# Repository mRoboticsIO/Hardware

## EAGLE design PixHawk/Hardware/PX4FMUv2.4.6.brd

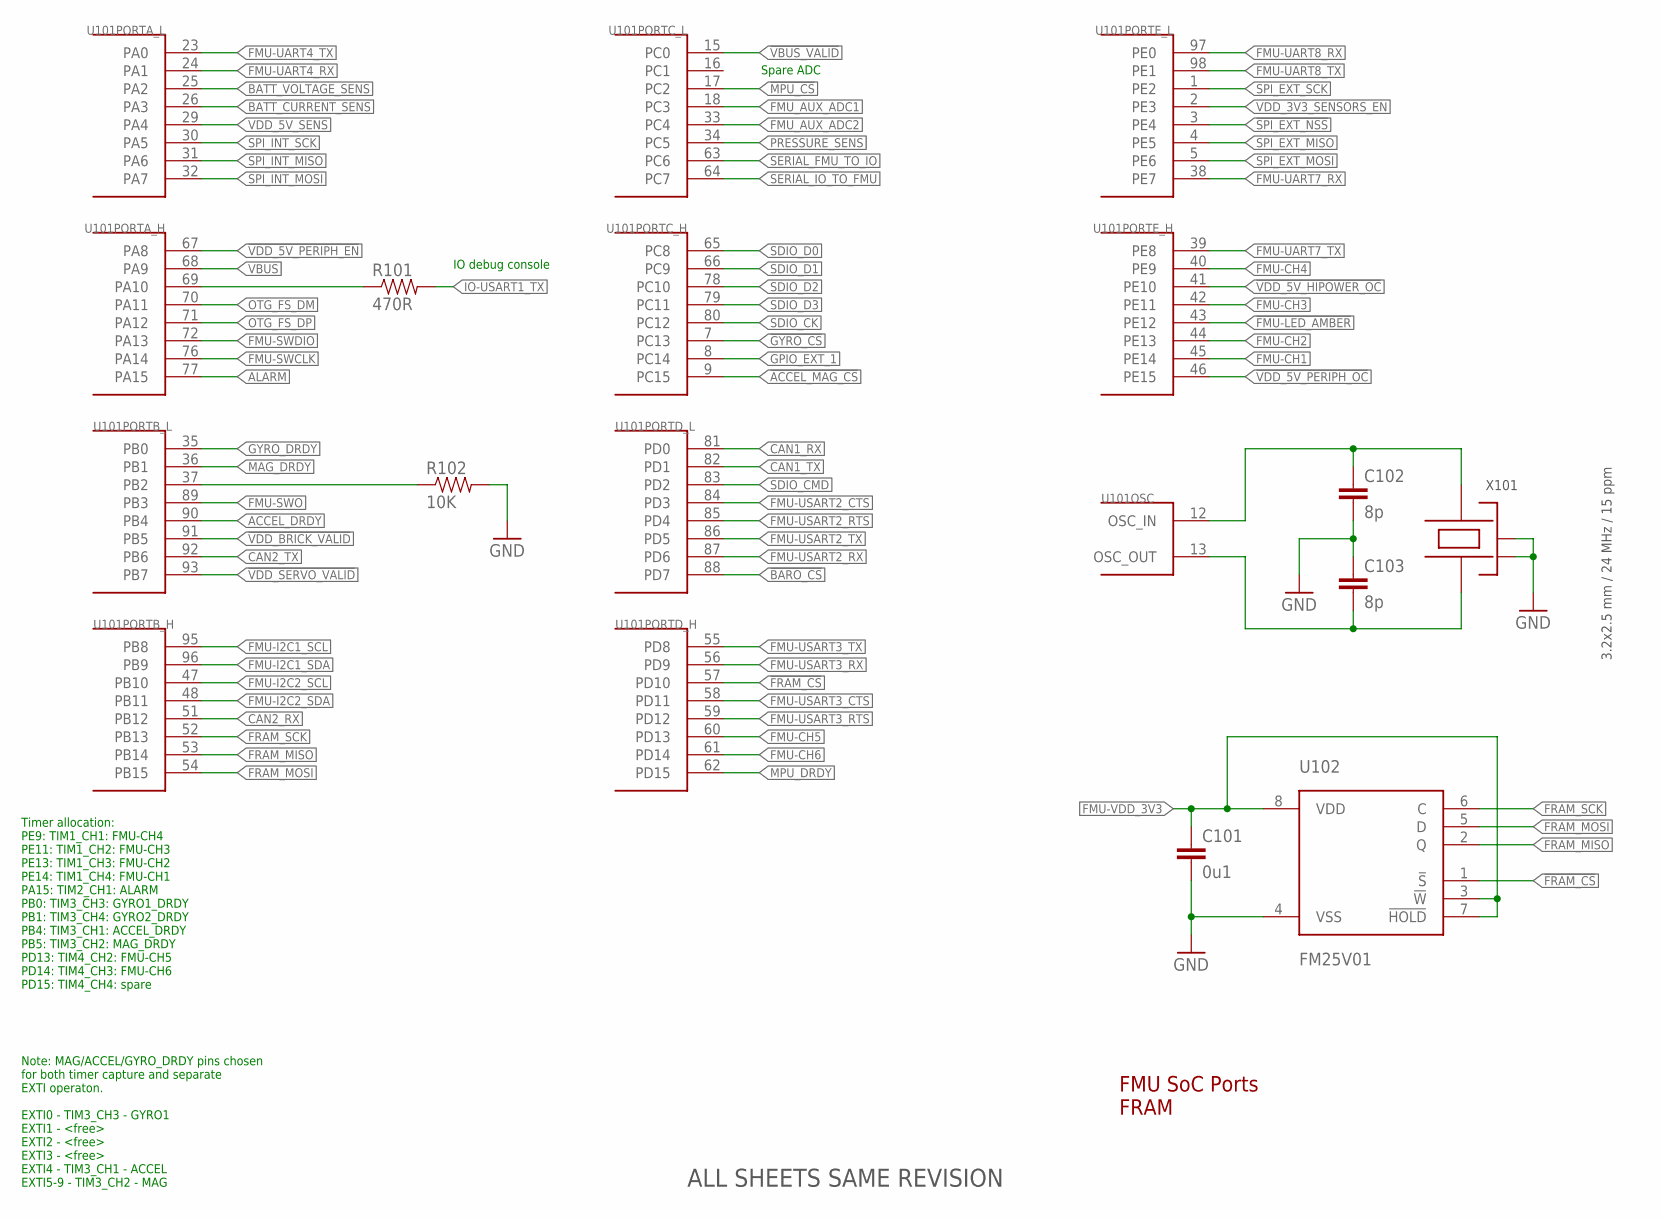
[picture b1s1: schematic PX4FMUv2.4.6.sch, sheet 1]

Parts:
C101: 0u1; 0402-CAP; PARTNO CC0402ZRY5V7BB104
C102, C103: 8p; 0402-CAP; PARTNO C1005C0G1H080C
R101: 470R; 0402-RES; PARTNO RC0402FR-07470RL
R102: 10K; 0402-RES; PARTNO RC0402FR-0710KL
U101: STM32F4X7VX; TQFP100; PARTNO STM32F427VI
U102: FM25V01; SO08; PARTNO FM25V01-G
X101: 3.2x2.5 mm / 24 MHz / 15 ppm; OSCILLATOR-3.2X2.5; PARTNO NX3225SA-24.000000MHZ

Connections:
!ACCEL_MAG_CS: U101.9 (PC15); also elsewhere on the board
!BARO_CS: U101.88 (PD7); also elsewhere on the board
!FMU-LED_AMBER: U101.43 (PE12); also elsewhere on the board
!FRAM_CS: U101.57 (PD10), U102.1 (!S)
!GYRO_CS: U101.7 (PC13); also elsewhere on the board
!MPU_CS: U101.17 (PC2); also elsewhere on the board
!SPI_EXT_NSS: U101.3 (PE4); also elsewhere on the board
!VBUS_VALID: U101.15 (PC0); also elsewhere on the board
!VDD_5V_HIPOWER_OC: U101.41 (PE10); also elsewhere on the board
!VDD_5V_PERIPH_EN: U101.67 (PA8); also elsewhere on the board
!VDD_5V_PERIPH_OC: U101.46 (PE15); also elsewhere on the board
!VDD_BRICK_VALID: U101.91 (PB5); also elsewhere on the board
!VDD_SERVO_VALID: U101.93 (PB7); also elsewhere on the board
ACCEL_DRDY: U101.90 (PB4); also elsewhere on the board
ALARM: U101.77 (PA15); also elsewhere on the board
BATT_CURRENT_SENS: U101.26 (PA3); also elsewhere on the board
BATT_VOLTAGE_SENS: U101.25 (PA2); also elsewhere on the board
CAN1_RX: U101.81 (PD0); also elsewhere on the board
CAN1_TX: U101.82 (PD1); also elsewhere on the board
CAN2_RX: U101.51 (PB12); also elsewhere on the board
CAN2_TX: U101.92 (PB6); also elsewhere on the board
FMU-CH1: U101.45 (PE14); also elsewhere on the board
FMU-CH2: U101.44 (PE13); also elsewhere on the board
FMU-CH3: U101.42 (PE11); also elsewhere on the board
FMU-CH4: U101.40 (PE9); also elsewhere on the board
FMU-CH5: U101.60 (PD13); also elsewhere on the board
FMU-CH6: U101.61 (PD14); also elsewhere on the board
FMU-I2C1_SCL: U101.95 (PB8); also elsewhere on the board
FMU-I2C1_SDA: U101.96 (PB9); also elsewhere on the board
FMU-I2C2_SCL: U101.47 (PB10); also elsewhere on the board
FMU-I2C2_SDA: U101.48 (PB11); also elsewhere on the board
FMU-SWCLK: U101.76 (PA14); also elsewhere on the board
FMU-SWDIO: U101.72 (PA13); also elsewhere on the board
FMU-SWO: U101.89 (PB3); also elsewhere on the board
FMU-UART4_RX: U101.24 (PA1); also elsewhere on the board
FMU-UART4_TX: U101.23 (PA0); also elsewhere on the board
FMU-UART7_RX: U101.38 (PE7); also elsewhere on the board
FMU-UART7_TX: U101.39 (PE8); also elsewhere on the board
FMU-UART8_RX: U101.97 (PE0); also elsewhere on the board
FMU-UART8_TX: U101.98 (PE1); also elsewhere on the board
FMU-USART2_CTS: U101.84 (PD3); also elsewhere on the board
FMU-USART2_RTS: U101.85 (PD4); also elsewhere on the board
FMU-USART2_RX: U101.87 (PD6); also elsewhere on the board
FMU-USART2_TX: U101.86 (PD5); also elsewhere on the board
FMU-USART3_CTS: U101.58 (PD11); also elsewhere on the board
FMU-USART3_RTS: U101.59 (PD12); also elsewhere on the board
FMU-USART3_RX: U101.56 (PD9); also elsewhere on the board
FMU-USART3_TX: U101.55 (PD8); also elsewhere on the board
FMU-VDD_3V3: C101.P$1 (1), U102.3 (!W), U102.7 (!HOLD), U102.8 (VDD); also elsewhere on the board
FMU_AUX_ADC1: U101.18 (PC3); also elsewhere on the board
FMU_AUX_ADC2: U101.33 (PC4); also elsewhere on the board
FRAM_MISO: U101.53 (PB14), U102.2 (Q)
FRAM_MOSI: U101.54 (PB15), U102.5 (D)
FRAM_SCK: U101.52 (PB13), U102.6 (C)
GND: C101.P$2 (2), C102.P$2 (2), C103.P$1 (1), R102.P$2 (2), U102.4 (VSS), X101.2 (NC_2), X101.4 (NC_4); also elsewhere on the board
GPIO_EXT_1: U101.8 (PC14); also elsewhere on the board
GYRO_DRDY: U101.35 (PB0); also elsewhere on the board
IO-USART1_TX: R101.P$2 (2); also elsewhere on the board
MAG_DRDY: U101.36 (PB1); also elsewhere on the board
MPU_DRDY: U101.62 (PD15); also elsewhere on the board
unnamed: C103.P$2 (2), U101.13 (OSC_OUT), X101.1
unnamed: C102.P$1 (1), U101.12 (OSC_IN), X101.3
unnamed: R101.P$1 (1), U101.69 (PA10)
OTG_FS_DM: U101.70 (PA11); also elsewhere on the board
OTG_FS_DP: U101.71 (PA12); also elsewhere on the board
PB2-BOOT1: R102.P$1 (1), U101.37 (PB2)
PRESSURE_SENS: U101.34 (PC5); also elsewhere on the board
SDIO_CK: U101.80 (PC12); also elsewhere on the board
SDIO_CMD: U101.83 (PD2); also elsewhere on the board
SDIO_D0: U101.65 (PC8); also elsewhere on the board
SDIO_D1: U101.66 (PC9); also elsewhere on the board
SDIO_D2: U101.78 (PC10); also elsewhere on the board
SDIO_D3: U101.79 (PC11); also elsewhere on the board
SERIAL_FMU_TO_IO: U101.63 (PC6); also elsewhere on the board
SERIAL_IO_TO_FMU: U101.64 (PC7); also elsewhere on the board
SPI_EXT_MISO: U101.4 (PE5); also elsewhere on the board
SPI_EXT_MOSI: U101.5 (PE6); also elsewhere on the board
SPI_EXT_SCK: U101.1 (PE2); also elsewhere on the board
SPI_INT_MISO: U101.31 (PA6); also elsewhere on the board
SPI_INT_MOSI: U101.32 (PA7); also elsewhere on the board
SPI_INT_SCK: U101.30 (PA5); also elsewhere on the board
VBUS: U101.68 (PA9); also elsewhere on the board
VDD_3V3_SENSORS_EN: U101.2 (PE3); also elsewhere on the board
VDD_5V_SENS: U101.29 (PA4); also elsewhere on the board

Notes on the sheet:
FMU SoC Ports FRAM
Note: MAG/ACCEL/GYRO_DRDY pins chosen for both timer capture and separate EXTI operaton. EXTI0 - TIM3_CH3 - GYRO1 EXTI1 - <free> EXTI2 - <free> EXTI3 - <free> EXTI4 - TIM3_CH1 - ACCEL EXTI5-9 - TIM3_CH2 - MAG
Timer allocation: PE9: TIM1_CH1: FMU-CH4 PE11: TIM1_CH2: FMU-CH3 PE13: TIM1_CH3: FMU-CH2 PE14: TIM1_CH4: FMU-CH1 PA15: TIM2_CH1: ALARM PB0: TIM3_CH3: GYRO1_DRDY PB1: TIM3_CH4: GYRO2_DRDY PB4: TIM3_CH1: ACCEL_DRDY PB5: TIM3_CH2: MAG_DRDY PD13: TIM4_CH2: FMU-CH5 PD14: TIM4_CH3: FMU-CH6 PD15: TIM4_CH4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
IO debug console
Spare ADC
ALL SHEETS SAME REVISION

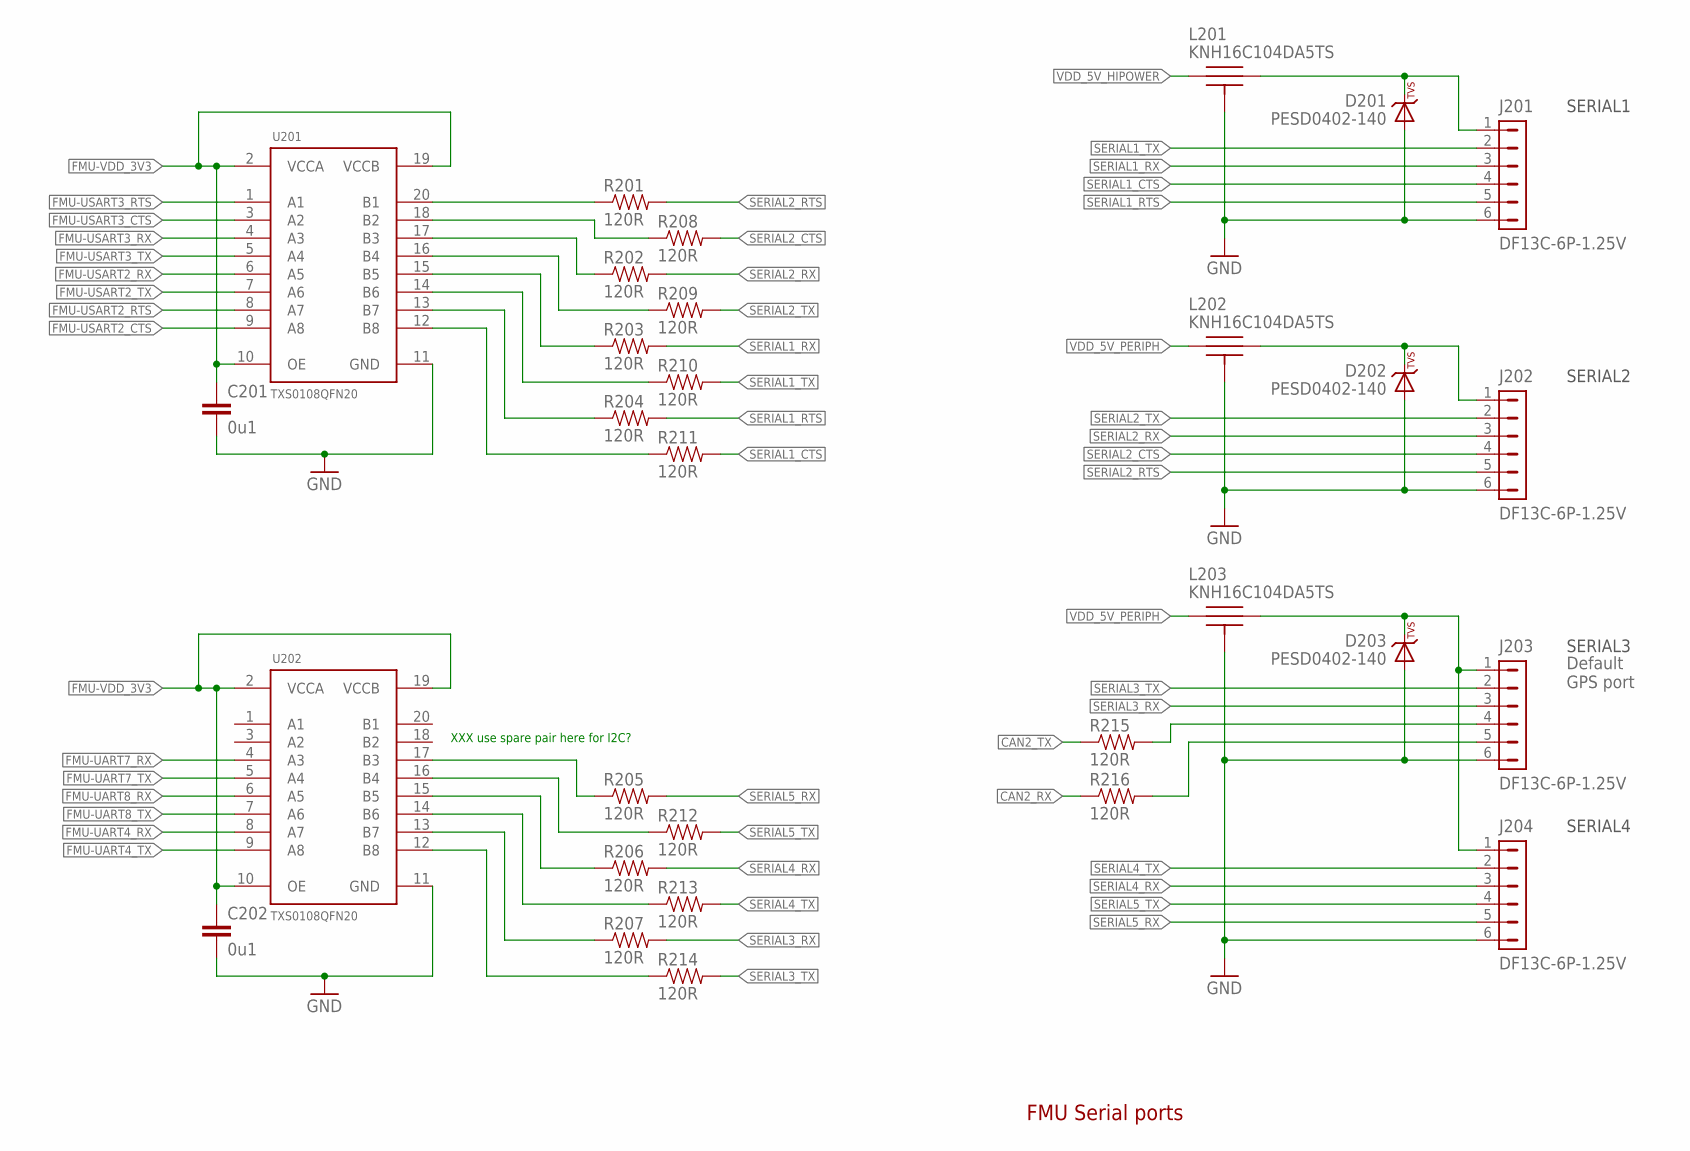
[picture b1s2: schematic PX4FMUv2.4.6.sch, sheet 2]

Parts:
C201, C202: 0u1; 0402-CAP; PARTNO CC0402ZRY5V7BB104
D201, D202, D203: PESD0402-140; 0402-TVS; PARTNO PESD0402-140
J201, J202, J203, J204: DF13C-6P-1.25V; PARTNO DF13C-6P-1.25V(20)
L201, L202, L203: KNH16C104DA5TS; KYOCERA-KNH16-DA; PARTNO KNH16C104DA5TS
R201, R202, R203, R204, R205, R206, R207, R208, R209, R210, R211, R212, R213, R214, R215, R216: 120R; 0402-RES; PARTNO RC0402FR-07120RL
U201, U202: TXS0108QFN20; QFN20-RGY; PARTNO TXS0108ERGYR

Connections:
CAN2_RX: R216.P$1 (1); also elsewhere on the board
CAN2_TX: R215.P$1 (1); also elsewhere on the board
FMU-UART4_RX: U202.8 (A7); also elsewhere on the board
FMU-UART4_TX: U202.9 (A8); also elsewhere on the board
FMU-UART7_RX: U202.4 (A3); also elsewhere on the board
FMU-UART7_TX: U202.5 (A4); also elsewhere on the board
FMU-UART8_RX: U202.6 (A5); also elsewhere on the board
FMU-UART8_TX: U202.7 (A6); also elsewhere on the board
FMU-USART2_CTS: U201.9 (A8); also elsewhere on the board
FMU-USART2_RTS: U201.8 (A7); also elsewhere on the board
FMU-USART2_RX: U201.6 (A5); also elsewhere on the board
FMU-USART2_TX: U201.7 (A6); also elsewhere on the board
FMU-USART3_CTS: U201.3 (A2); also elsewhere on the board
FMU-USART3_RTS: U201.1 (A1); also elsewhere on the board
FMU-USART3_RX: U201.4 (A3); also elsewhere on the board
FMU-USART3_TX: U201.5 (A4); also elsewhere on the board
FMU-VDD_3V3: C201.P$1 (1), C202.P$1 (1), U201.2 (VCCA), U201.10 (OE), U201.19 (VCCB), U202.2 (VCCA), U202.10 (OE), U202.19 (VCCB); also elsewhere on the board
GND: C201.P$2 (2), C202.P$2 (2), D201.A, D202.A, D203.A, J201.6, J202.6, J203.6, J204.6, L201.P$3, L201.P$4, L201.P$5, L202.P$3, L202.P$4, L202.P$5, L203.P$3, L203.P$4, L203.P$5, U201.11 (GND), U202.11 (GND); also elsewhere on the board
unnamed: D201.C, J201.1, L201.P$2
unnamed: J203.4, R215.P$2 (2)
unnamed: J203.5, R216.P$2 (2)
unnamed: R201.P$1 (1), U201.20 (B1)
unnamed: R208.P$1 (1), U201.18 (B2)
unnamed: R202.P$1 (1), U201.17 (B3)
unnamed: R209.P$1 (1), U201.16 (B4)
unnamed: R203.P$1 (1), U201.15 (B5)
unnamed: R210.P$1 (1), U201.14 (B6)
unnamed: R204.P$1 (1), U201.13 (B7)
unnamed: R211.P$1 (1), U201.12 (B8)
unnamed: R207.P$1 (1), U202.13 (B7)
unnamed: R214.P$1 (1), U202.12 (B8)
unnamed: R205.P$1 (1), U202.17 (B3)
unnamed: R212.P$1 (1), U202.16 (B4)
unnamed: R206.P$1 (1), U202.15 (B5)
unnamed: R213.P$1 (1), U202.14 (B6)
unnamed: D203.C, J203.1, J204.1, L203.P$2
unnamed: D202.C, J202.1, L202.P$2
SERIAL1_CTS: J201.4, R211.P$2 (2)
SERIAL1_RTS: J201.5, R204.P$2 (2)
SERIAL1_RX: J201.3, R203.P$2 (2); also elsewhere on the board
SERIAL1_TX: J201.2, R210.P$2 (2); also elsewhere on the board
SERIAL2_CTS: J202.4, R208.P$2 (2)
SERIAL2_RTS: J202.5, R201.P$2 (2)
SERIAL2_RX: J202.3, R202.P$2 (2); also elsewhere on the board
SERIAL2_TX: J202.2, R209.P$2 (2); also elsewhere on the board
SERIAL3_RX: J203.3, R207.P$2 (2); also elsewhere on the board
SERIAL3_TX: J203.2, R214.P$2 (2); also elsewhere on the board
SERIAL4_RX: J204.3, R206.P$2 (2); also elsewhere on the board
SERIAL4_TX: J204.2, R213.P$2 (2); also elsewhere on the board
SERIAL5_RX: J204.5, R205.P$2 (2); also elsewhere on the board
SERIAL5_TX: J204.4, R212.P$2 (2); also elsewhere on the board
VDD_5V_HIPOWER: L201.P$1; also elsewhere on the board
VDD_5V_PERIPH: L202.P$1, L203.P$1; also elsewhere on the board

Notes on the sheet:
FMU Serial ports
XXX use spare pair here for I2C?
SERIAL2
SERIAL1
SERIAL3
SERIAL4
Default GPS port

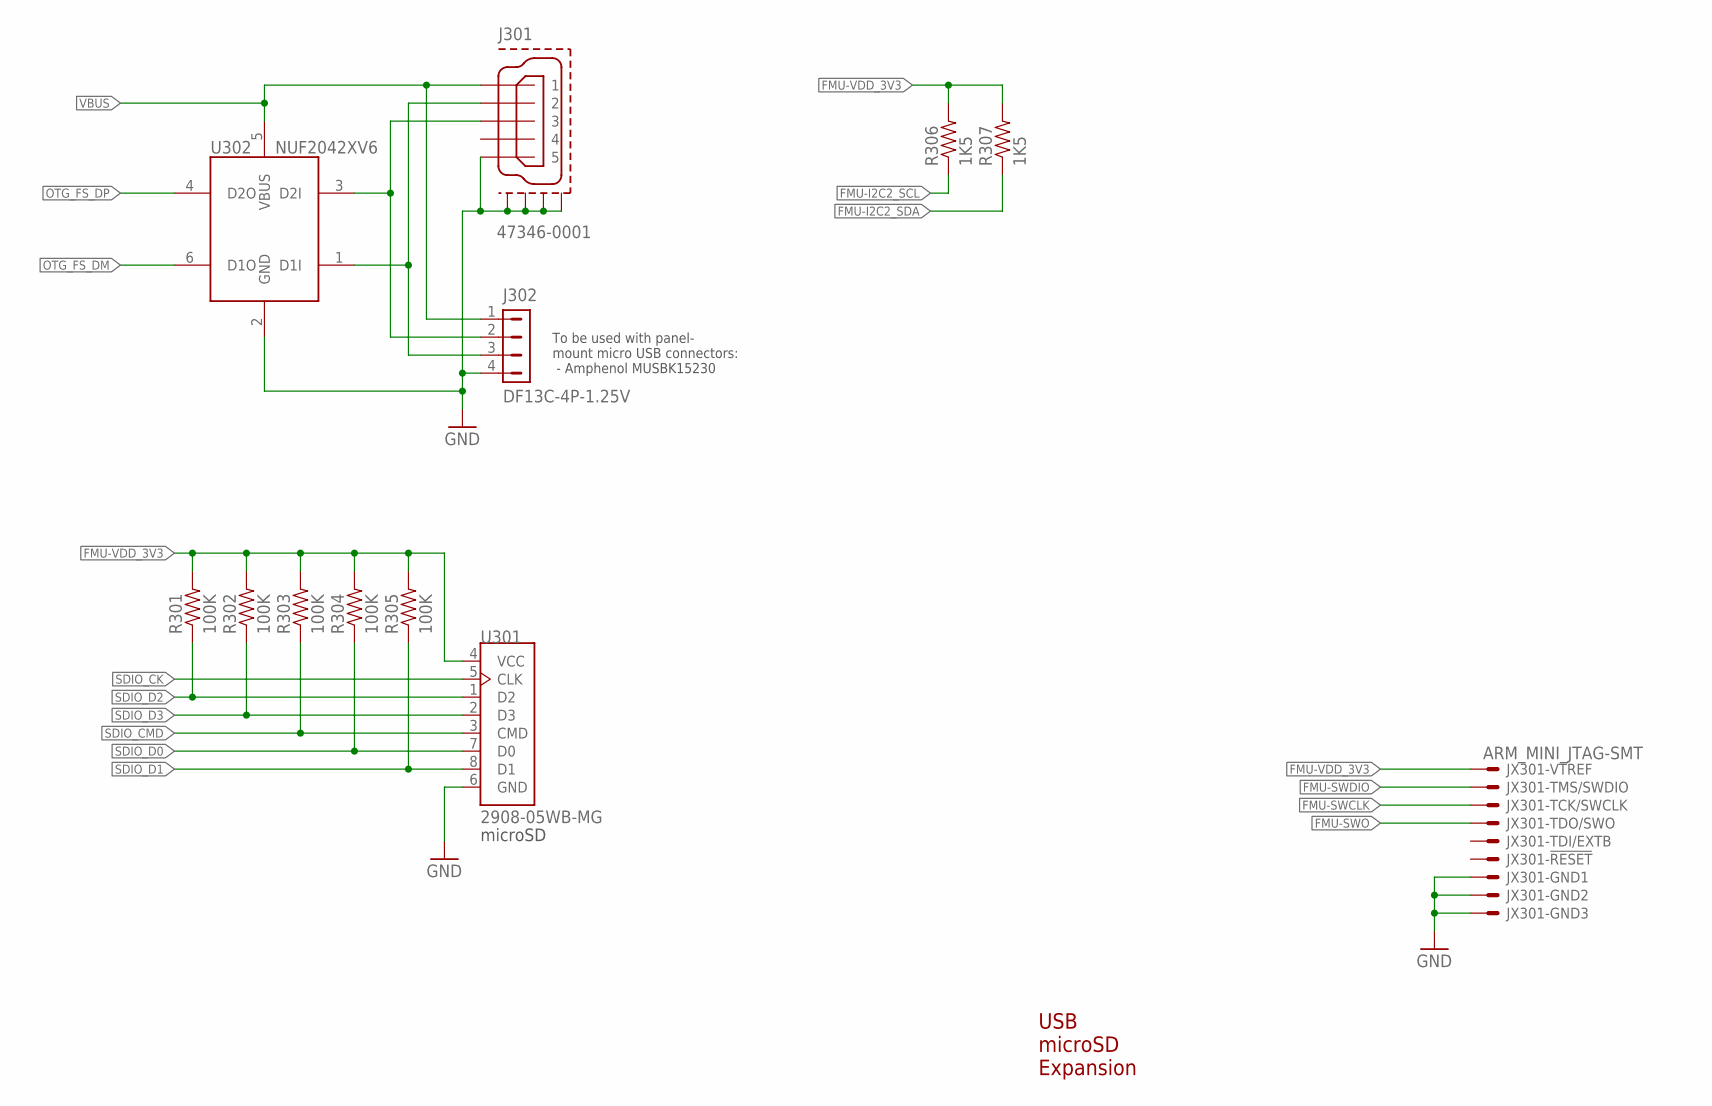
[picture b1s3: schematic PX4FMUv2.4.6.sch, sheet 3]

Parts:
J301: 47346-0001; MOLEX-47346-0001; PARTNO 47346-0001
J302: DF13C-4P-1.25V; PARTNO DF13C-4P-1.25V(20)
JX301: ARM_MINI_JTAG-SMT; FTSH-105-01-XXX-DV-K; PARTNO M50-3900542
R301, R302, R303, R304, R305: 100K; 0402-RES; PARTNO RC0402FR-07100KL
R306, R307: 1K5; 0402-RES; PARTNO RC0402FR-071K5L
U301: 2908-05WB-MG; MICROSD; PARTNO 2908-05WB-MG
U302: NUF2042XV6; SOT563-6; PARTNO NUF2042XV6T1G

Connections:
FMU-I2C2_SCL: R306.P$1 (1); also elsewhere on the board
FMU-I2C2_SDA: R307.P$1 (1); also elsewhere on the board
FMU-SWCLK: JX301.4; also elsewhere on the board
FMU-SWDIO: JX301.2; also elsewhere on the board
FMU-SWO: JX301.6; also elsewhere on the board
FMU-VDD_3V3: JX301.1, R301.P$2 (2), R302.P$2 (2), R303.P$2 (2), R304.P$2 (2), R305.P$2 (2), R306.P$2 (2), R307.P$2 (2), U301.4 (VCC); also elsewhere on the board
GND: J301.GND (5), J301.GND1, J301.GND2, J301.GND3, J301.GND4, J302.4, JX301.3, JX301.5, JX301.9, U301.6 (GND), U302.2 (GND); also elsewhere on the board
OTG_DM1: J301.D- (2), J302.3, U302.1 (D1I)
OTG_DP1: J301.D+ (3), J302.2, U302.3 (D2I)
OTG_FS_DM: U302.6 (D1O); also elsewhere on the board
OTG_FS_DP: U302.4 (D2O); also elsewhere on the board
SDIO_CK: U301.5 (CLK); also elsewhere on the board
SDIO_CMD: R303.P$1 (1), U301.3 (CMD); also elsewhere on the board
SDIO_D0: R304.P$1 (1), U301.7 (D0); also elsewhere on the board
SDIO_D1: R305.P$1 (1), U301.8 (D1); also elsewhere on the board
SDIO_D2: R301.P$1 (1), U301.1 (D2); also elsewhere on the board
SDIO_D3: R302.P$1 (1), U301.2 (D3); also elsewhere on the board
VBUS: J301.VBUS (1), J302.1, U302.5 (VBUS); also elsewhere on the board

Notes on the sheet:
USB microSD Expansion
microSD
To be used with panel- mount micro USB connectors: - Amphenol MUSBK15230

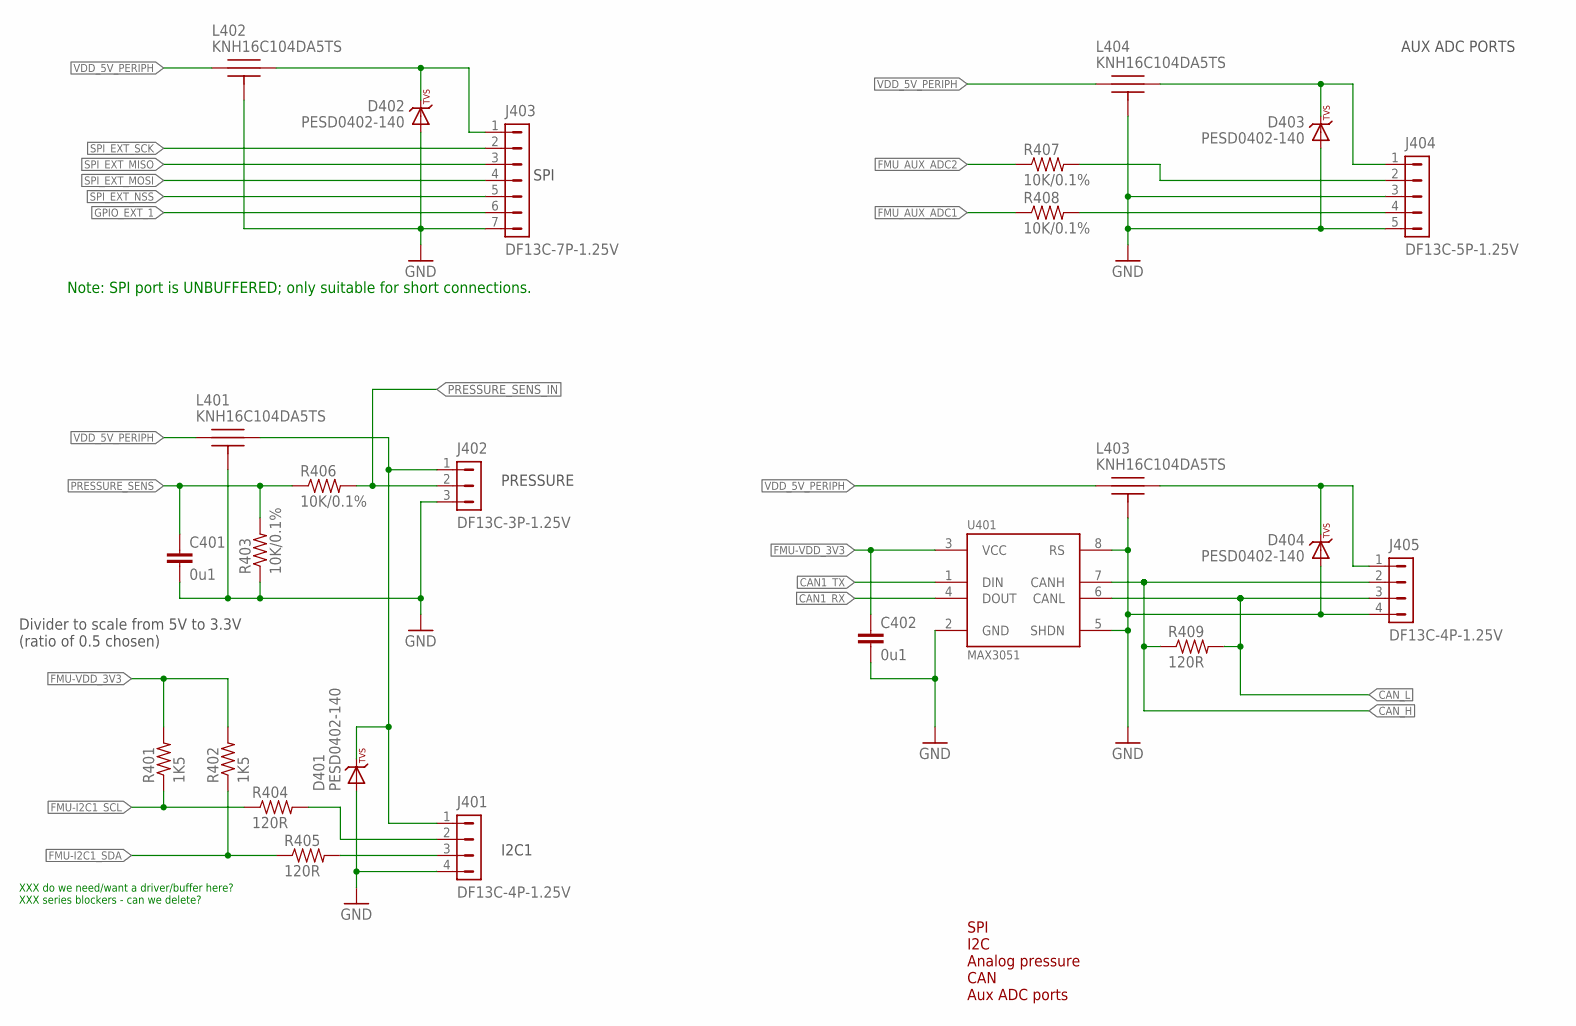
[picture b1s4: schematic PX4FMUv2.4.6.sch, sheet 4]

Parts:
C401, C402: 0u1; 0402-CAP; PARTNO CC0402ZRY5V7BB104
D401, D402, D403, D404: PESD0402-140; 0402-TVS; PARTNO PESD0402-140
J401, J405: DF13C-4P-1.25V; PARTNO DF13C-4P-1.25V(20)
J402: DF13C-3P-1.25V; PARTNO DF13C-3P-1.25V(20)
J403: DF13C-7P-1.25V; PARTNO DF13C-7P-1.25V(20)
J404: DF13C-5P-1.25V; PARTNO DF13C-5P-1.25V(20)
L401, L402, L403, L404: KNH16C104DA5TS; KYOCERA-KNH16-DA; PARTNO KNH16C104DA5TS
R401, R402: 1K5; 0402-RES; PARTNO RC0402FR-071K5L
R403, R406, R407, R408: 10K/0.1%; 0402-RES; PARTNO ERA-2AEB103X
R404, R405, R409: 120R; 0402-RES; PARTNO RC0402FR-07120RL
U401: MAX3051; SOT23-8; PARTNO MAX3051EKA

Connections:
!SPI_EXT_NSS: J403.5; also elsewhere on the board
CAN1_RX: U401.4 (DOUT); also elsewhere on the board
CAN1_TX: U401.1 (DIN); also elsewhere on the board
CAN_H: J405.2, R409.P$1 (1), U401.7 (CANH); also elsewhere on the board
CAN_L: J405.3, R409.P$2 (2), U401.6 (CANL); also elsewhere on the board
FMU-I2C1_SCL: R401.P$1 (1), R404.P$1 (1); also elsewhere on the board
FMU-I2C1_SDA: R402.P$1 (1), R405.P$1 (1); also elsewhere on the board
FMU-VDD_3V3: C402.P$1 (1), R401.P$2 (2), R402.P$2 (2), U401.3 (VCC); also elsewhere on the board
FMU_AUX_ADC1: R408.P$1 (1); also elsewhere on the board
FMU_AUX_ADC1_PROT: J404.4, R408.P$2 (2)
FMU_AUX_ADC2: R407.P$1 (1); also elsewhere on the board
FMU_AUX_ADC2_PROT: J404.2, R407.P$2 (2)
GND: C401.P$2 (2), C402.P$2 (2), D401.A, D402.A, D403.A, D404.A, J401.4, J402.3, J403.7, J404.3, J404.5, J405.4, L401.P$3, L401.P$4, L401.P$5, L402.P$3, L402.P$4, L402.P$5, L403.P$3, L403.P$4, L403.P$5, L404.P$3, L404.P$4, L404.P$5, R403.P$1 (1), U401.2 (GND), U401.5 (SHDN), U401.8 (RS); also elsewhere on the board
GPIO_EXT_1: J403.6; also elsewhere on the board
unnamed: J401.2, R404.P$2 (2)
unnamed: J401.3, R405.P$2 (2)
unnamed: D402.C, J403.1, L402.P$2
unnamed: D401.C, J401.1, J402.1, L401.P$2
unnamed: D404.C, J405.1, L403.P$2
unnamed: D403.C, J404.1, L404.P$2
PRESSURE_SENS: C401.P$1 (1), R403.P$2 (2), R406.P$1 (1); also elsewhere on the board
PRESSURE_SENS_IN: J402.2, R406.P$2 (2); also elsewhere on the board
SPI_EXT_MISO: J403.3; also elsewhere on the board
SPI_EXT_MOSI: J403.4; also elsewhere on the board
SPI_EXT_SCK: J403.2; also elsewhere on the board
VDD_5V_PERIPH: L401.P$1, L402.P$1, L403.P$1, L404.P$1; also elsewhere on the board

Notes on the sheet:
SPI
PRESSURE
XXX do we need/want a driver/buffer here? XXX series blockers - can we delete?
I2C1
AUX ADC PORTS
SPI I2C Analog pressure CAN Aux ADC ports
Note: SPI port is UNBUFFERED; only suitable for short connections.
Divider to scale from 5V to 3.3V (ratio of 0.5 chosen)

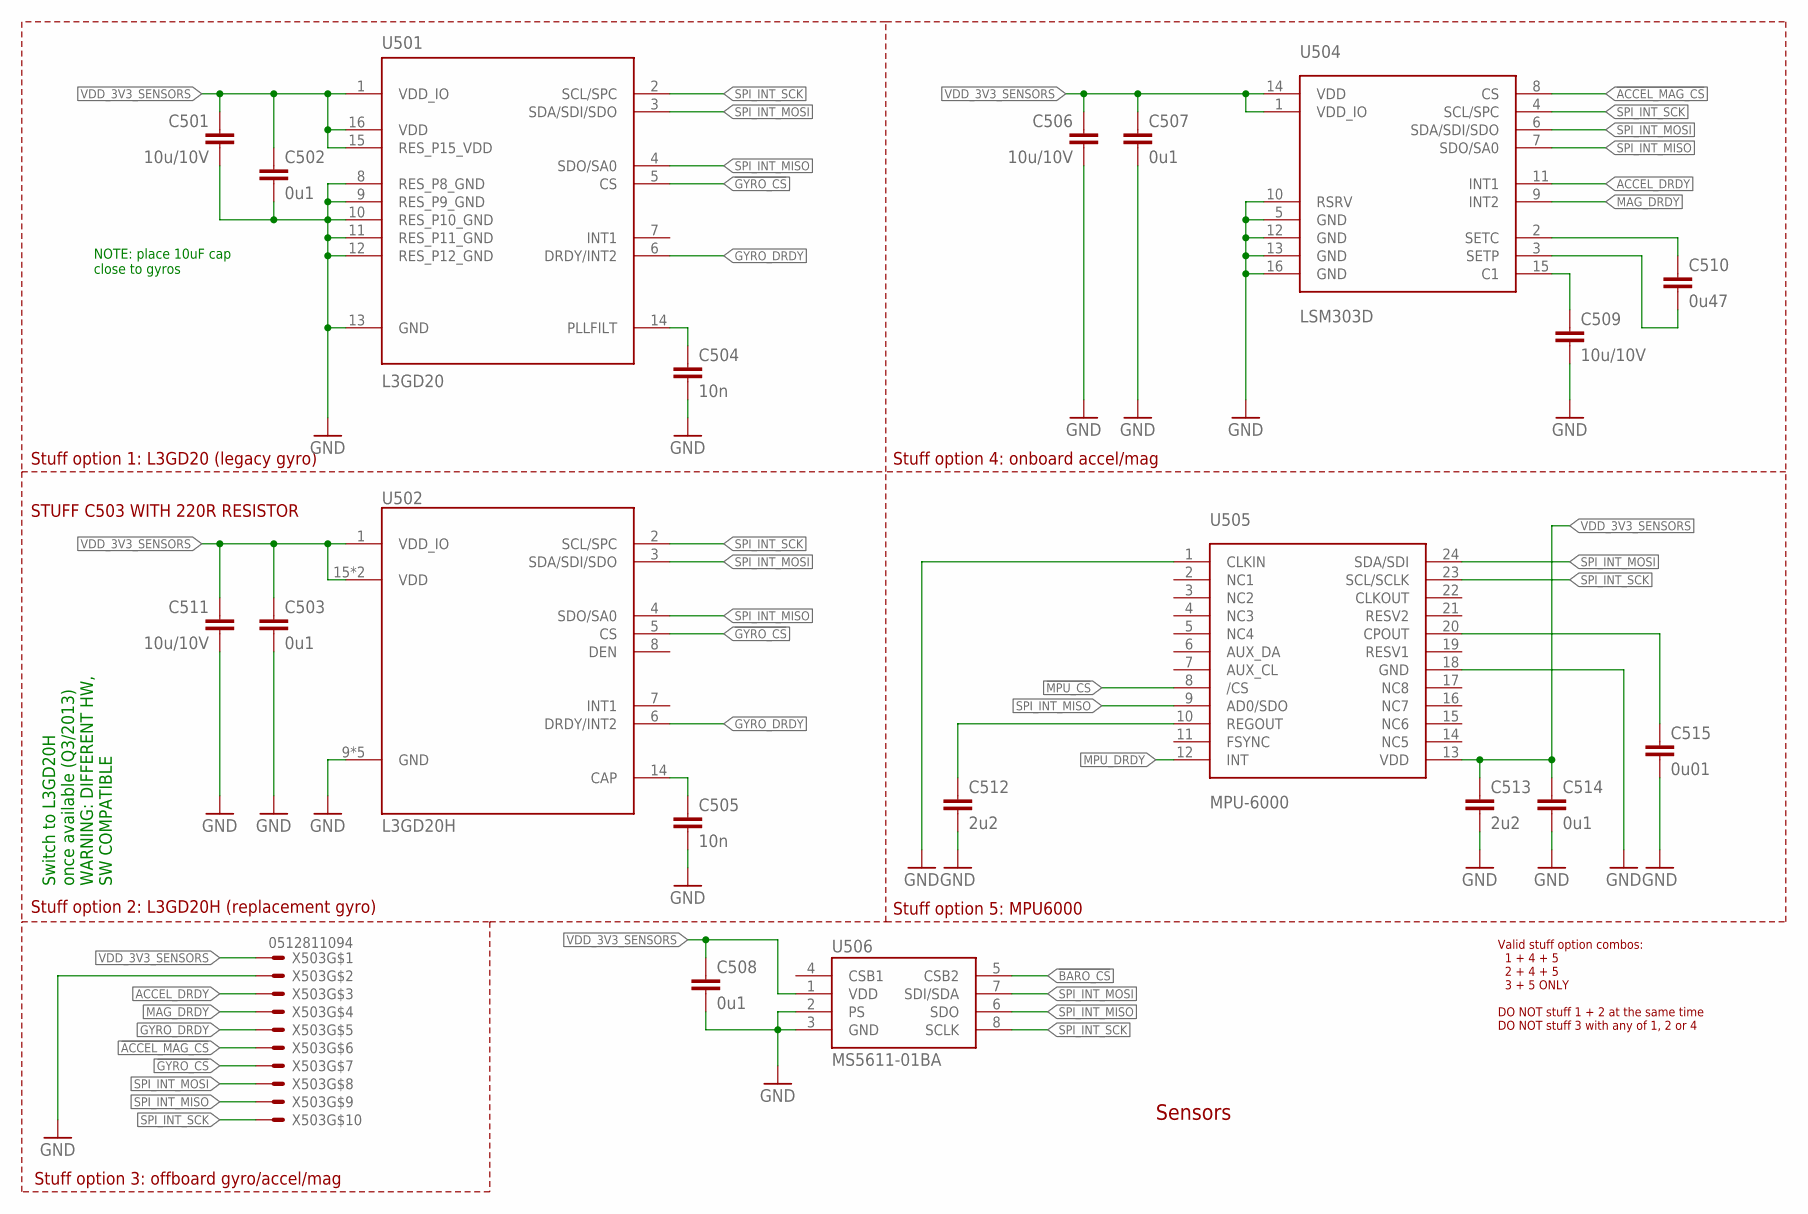
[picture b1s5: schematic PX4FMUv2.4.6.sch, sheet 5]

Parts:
C501, C506, C509, C511: 10u/10V; 0805-CAP; PARTNO CC0805ZKY5V6BB106
C502, C503, C507, C508, C514: 0u1; 0402-CAP; PARTNO CC0402ZRY5V7BB104
C504, C505: 10n; 0402-CAP; PARTNO CC0402KRX7R7BB103
C510: 0u47; 0402-CAP; PARTNO C1005X5R1C474K050BC
C512, C513: 2u2; 0603-CAP; PARTNO C1608X6S1C225K080AC
C515: 0u01; 0603-CAP; PARTNO 06033C103JAT2A
U501: L3GD20; L3G4200DH-MAN; PARTNO L3GD20
U502: L3GD20H; LGA-16L; PARTNO L3GD20H
U504: LSM303D; LGA-16L; PARTNO LSM303D
U505: MPU-6000; QFN-24; PARTNO MPU-6000
U506: MS5611-01BA; PARTNO MS5611-01BA
X503: 0512811094; 51281-1094; PARTNO 0781191109

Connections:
!ACCEL_MAG_CS: U504.8 (CS), X503.6; also elsewhere on the board
!BARO_CS: U506.5 (CSB2); also elsewhere on the board
!GYRO_CS: U501.5 (CS), U502.5 (CS), X503.7; also elsewhere on the board
!MPU_CS: U505.8 (/CS); also elsewhere on the board
ACCEL_DRDY: U504.11 (INT1), X503.3; also elsewhere on the board
GND: C501.P$2 (2), C502.P$2 (2), C503.P$2 (2), C504.P$2 (2), C505.P$2 (2), C506.P$2 (2), C507.P$2 (2), C508.P$2 (2), C509.P$2 (2), C511.P$2 (2), C512.P$2 (2), C513.P$2 (2), C514.P$2 (2), C515.P$2 (2), U501.8 (RES_P8_GND), U501.9 (RES_P9_GND), U501.10 (RES_P10_GND), U501.11 (RES_P11_GND), U501.12 (RES_P12_GND), U501.13 (GND), U502.9 (GND), U502.10 (GND), U502.11 (GND), U502.12 (GND), U502.13 (GND), U504.5 (GND), U504.10 (RSRV), U504.12 (GND), U504.13 (GND), U504.16 (GND), U505.1 (CLKIN), U505.18 (GND), U506.2 (PS), U506.3 (GND), X503.2; also elsewhere on the board
GYRO_DRDY: U501.6 (DRDY/INT2), U502.6 (DRDY/INT2), X503.5; also elsewhere on the board
MAG_DRDY: U504.9 (INT2), X503.4; also elsewhere on the board
MPU_DRDY: U505.12 (INT); also elsewhere on the board
unnamed: C509.P$1 (1), U504.15 (C1)
unnamed: C510.P$1 (1), U504.2 (SETC)
unnamed: C510.P$2 (2), U504.3 (SETP)
unnamed: C505.P$1 (1), U502.14 (CAP)
unnamed: C504.P$1 (1), U501.14 (PLLFILT)
unnamed: C512.P$1 (1), U505.10 (REGOUT)
unnamed: C515.P$1 (1), U505.20 (CPOUT)
SPI_INT_MISO: U501.4 (SDO/SA0), U502.4 (SDO/SA0), U504.7 (SDO/SA0), U505.9 (AD0/SDO), U506.6 (SDO), X503.9; also elsewhere on the board
SPI_INT_MOSI: U501.3 (SDA/SDI/SDO), U502.3 (SDA/SDI/SDO), U504.6 (SDA/SDI/SDO), U505.24 (SDA/SDI), U506.7 (SDI/SDA), X503.8; also elsewhere on the board
SPI_INT_SCK: U501.2 (SCL/SPC), U502.2 (SCL/SPC), U504.4 (SCL/SPC), U505.23 (SCL/SCLK), U506.8 (SCLK), X503.10; also elsewhere on the board
VDD_3V3_SENSORS: C501.P$1 (1), C502.P$1 (1), C503.P$1 (1), C506.P$1 (1), C507.P$1 (1), C508.P$1 (1), C511.P$1 (1), C513.P$1 (1), C514.P$1 (1), U501.1 (VDD_IO), U501.15 (RES_P15_VDD), U501.16 (VDD), U502.1 (VDD_IO), U502.15 (VDD), U502.16 (VDD), U504.1 (VDD_IO), U504.14 (VDD), U505.13 (VDD), U506.1 (VDD), X503.1; also elsewhere on the board

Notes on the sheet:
Sensors
Switch to L3GD20H once available (Q3/2013) WARNING: DIFFERENT HW, SW COMPATIBLE
NOTE: place 10uF cap close to gyros
Stuff option 1: L3GD20 (legacy gyro)
Stuff option 2: L3GD20H (replacement gyro)
Stuff option 4: onboard accel/mag
Valid stuff option combos: 1 + 4 + 5 2 + 4 + 5 3 + 5 ONLY DO NOT stuff 1 + 2 at the same time DO NOT stuff 3 with any of 1, 2 or 4
Stuff option 5: MPU6000
Stuff option 3: offboard gyro/accel/mag
STUFF C503 WITH 220R RESISTOR

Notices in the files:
PixHawk/Hardware/PX4FMUv2.4.6.brd:
(c) 2013 mjs/lm/jo
